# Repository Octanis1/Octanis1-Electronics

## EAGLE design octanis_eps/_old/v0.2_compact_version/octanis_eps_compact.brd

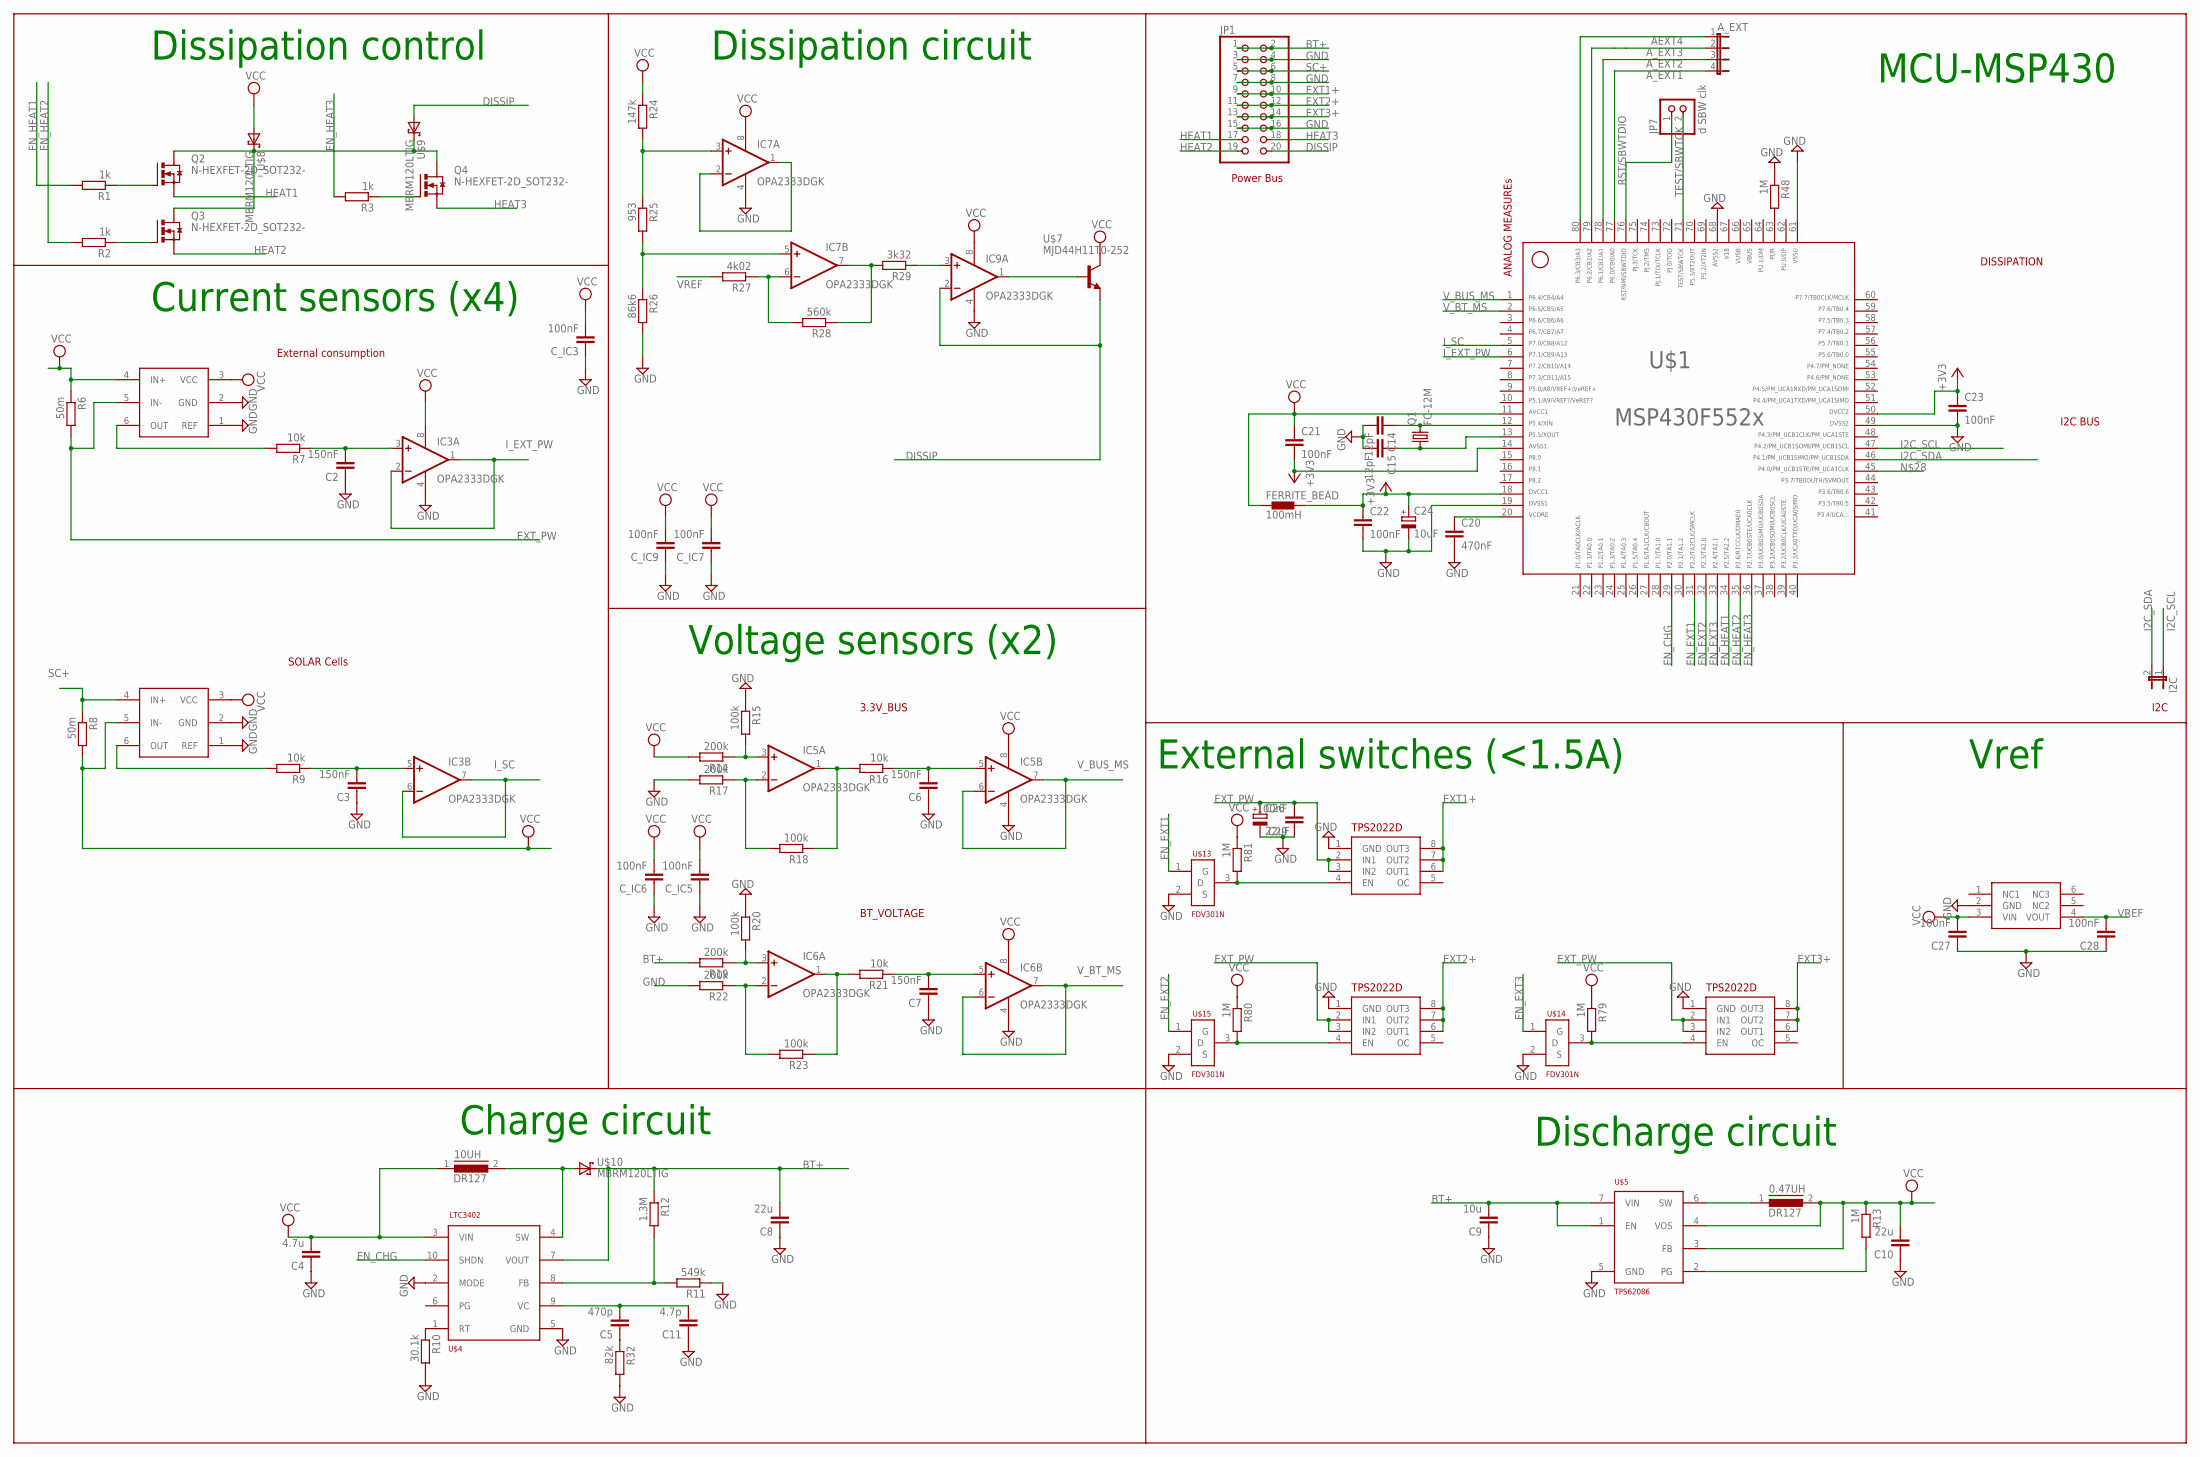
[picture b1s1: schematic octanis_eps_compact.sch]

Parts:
0.47UH, 10UH: DR127
A_EXT: JP4E; JP4
C2, C3, C6, C7: 150nF; C0603
C4: 4.7u; C1206
C5: 470p; C0603
C8: 22u; C0603
C9: 10u; C1206
C10: 22u; C1206
C11: 4.7p; C0603
C14, C15: 12pF; C0603
C20: 470nF; C0603
C21, C22, C23, C27, C28, C29: 100nF; C0603
C24: 10uF; A/3216-18R
C26: 22uF; A/3216-18R
C_IC3, C_IC5, C_IC6, C_IC7, C_IC9: 100nF; C0603
FERRITE_BEAD: 100mH; 0402
I2C: JP1E; JP1
IC3, IC5, IC6, IC7, IC9: OPA2333DGK; MSOP08
JP1: PINHD-2X10; 2X10
JP7: d SBW clk; 1X02
Q1: FC-12M
Q2, Q3, Q4: N-HEXFET-2D_SOT232-; SOT223
R1, R2, R3: 1k; R0603
R6, R8: 50m; R1206
R7, R9, R16, R21: 10k; R0603
R10: 30.1k; R0603
R11: 549k; R0603
R12: 1.3M; R0603
R13, R48, R79, R80, R81: 1M; R0603
R14, R17, R19, R22: 200k; R0603
R15, R18, R20, R23: 100k; R0603
R24: 147k; R0603
R25: 953; R0603
R26: 86k6; R0603
R27: 4k02; R0603
R28: 560k; R0603
R29: 3k32; R0603
R32: 82k; R0603
U$1: F552X---PN80; PN80
U$2, U$3: INA213; SC70-6
U$4: LTC3402; MSOP10
U$5: TPS62086; QFN-7
U$7: MJD44H11T0-252; TO252
U$8, U$9, U$10: MBRM120LTIG; DO216AA
U$13, U$14, U$15: FDV301N; SOT23
U$16, U$17, U$18: TPS2022D; SO8
U$19: ADR127B; TSOT23-6

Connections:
65: U$1.65
66: U$1.66
67: U$1.67
+3V3: C21.2, C22.1, C23.1, C24.+, FERRITE_BEAD.2, U$1.14, U$1.18, U$1.50
AEXT4: A_EXT.1, U$1.80
A_EXT1: A_EXT.4, U$1.77
A_EXT2: A_EXT.3, U$1.78
A_EXT3: A_EXT.2, U$1.79
BT+: C8.2, C9.2, JP1.1, JP1.2, R12.1, R19.2, U$4.7 (VOUT), U$5.1 (EN), U$5.7 (VIN), U$10.C (K)
DISSIP: IC9.2 (-IN), JP1.20, U$7.3 (E), U$9.A
EN_CHG: U$1.29, U$4.10 (SHDN)
EN_EXT1: U$1.31, U$13.1 (G)
EN_EXT2: U$1.32, U$15.1 (G)
EN_EXT3: U$1.33, U$14.1 (G)
EN_HEAT1: R1.2, U$1.34
EN_HEAT2: R2.2, U$1.35
EN_HEAT3: R3.2, U$1.36
EXT1+: JP1.9, JP1.10, U$16.6 (OUT1), U$16.7 (OUT2), U$16.8 (OUT3)
EXT2+: JP1.11, JP1.12, U$17.6 (OUT1), U$17.7 (OUT2), U$17.8 (OUT3)
EXT3+: JP1.13, JP1.14, U$18.6 (OUT1), U$18.7 (OUT2), U$18.8 (OUT3)
EXT_PW: C26.+, C29.2, R6.2, U$2.5 (IN-), U$16.2 (IN1), U$16.3 (IN2), U$17.2 (IN1), U$17.3 (IN2), U$18.2 (IN1), U$18.3 (IN2)
GND: C2.1, C3.1, C4.1, C6.1, C7.1, C8.1, C9.1, C10.1, C11.1, C14.2, C15.2, C20.2, C22.2, C23.2, C24.-, C26.-, C27.1, C28.1, C29.1, C_IC3.1, C_IC5.1, C_IC6.1, C_IC7.1, C_IC9.1, IC3.4 (V-), IC5.4 (V-), IC6.4 (V-), IC7.4 (V-), IC9.4 (V-), JP1.3, JP1.4, JP1.7, JP1.8, JP1.15, JP1.16, R10.2, R11.1, R15.1, R17.2, R20.1, R22.2, R26.2, R32.2, R48.1, U$1.19, U$1.49, U$1.61, U$1.68, U$2.1 (REF), U$2.2 (GND), U$3.1 (REF), U$3.2 (GND), U$4.2 (MODE), U$4.5 (GND), U$5.5 (GND), U$13.2 (S), U$14.2 (S), U$15.2 (S), U$16.1 (GND), U$17.1 (GND), U$18.1 (GND), U$19.2 (GND)
HEAT1: JP1.17, Q2.3 (S)
HEAT2: JP1.19, Q3.3 (S)
HEAT3: JP1.18, Q4.3 (S)
I2C_SCL: I2C.1, U$1.47
I2C_SDA: I2C.2, U$1.46
I_EXT_PW: IC3.1 (OUT), IC3.2 (-IN), U$1.6
I_SC: IC3.6 (-IN), IC3.7 (OUT), U$1.5
unnamed: R7.2, U$2.6 (OUT)
unnamed: R9.2, U$3.6 (OUT)
unnamed: R10.1, U$4.1 (RT)
unnamed: C5.1, R32.1
unnamed: Q2.2 (D), Q2.4 (D), Q3.2 (D), Q3.4 (D), Q4.2 (D), Q4.4 (D), U$8.C (K), U$9.C (K)
unnamed: C2.2, IC3.3 (+IN), R7.1
unnamed: C3.2, IC3.5 (+IN), R9.1
unnamed: C5.2, C11.2, U$4.9 (VC)
unnamed: C7.2, IC6.5 (+IN), R21.1
unnamed: IC6.1 (OUT), R21.2, R23.1
unnamed: C6.2, IC5.5 (+IN), R16.1
unnamed: IC5.1 (OUT), R16.2, R18.1
unnamed: IC5.2 (-IN), R17.1, R18.2
unnamed: IC5.3 (+IN), R14.1, R15.2
unnamed: IC6.2 (-IN), R22.1, R23.2
unnamed: IC6.3 (+IN), R19.1, R20.2
unnamed: IC7.1 (OUT), IC7.2 (-IN)
unnamed: IC7.3 (+IN), R24.2, R25.1
unnamed: IC7.5 (+IN), R25.2, R26.1
unnamed: IC7.6 (-IN), R27.1, R28.2
unnamed: IC7.7 (OUT), R28.1, R29.2
unnamed: IC9.3 (+IN), R29.1
unnamed: R11.2, R12.2, U$4.8 (FB)
unnamed: 10UH.2, U$4.4 (SW), U$10.A
unnamed: R13.2, U$5.2 (PG)
unnamed: 0.47UH.1, U$5.6 (SW)
unnamed: R48.2, U$1.63
unnamed: Q2.1 (G), R1.1
unnamed: Q3.1 (G), R2.1
unnamed: R80.2, U$15.3 (D), U$17.4 (EN)
unnamed: Q4.1 (G), R3.1
unnamed: IC9.1 (OUT), U$7.1 (B)
unnamed: C14.1, Q1.2, U$1.12
unnamed: C20.1, U$1.20
unnamed: C15.1, Q1.1, U$1.13
unnamed: R81.2, U$13.3 (D), U$16.4 (EN)
unnamed: R79.2, U$14.3 (D), U$18.4 (EN)
RST/SBWTDIO: JP7.1, U$1.76
SC+: JP1.5, JP1.6, R8.1, U$3.4 (IN+)
TEST/SBWTCK: JP7.2, U$1.71
VCC: 0.47UH.2, 10UH.1, C4.2, C10.2, C21.1, C27.2, C_IC3.2, C_IC5.2, C_IC6.2, C_IC7.2, C_IC9.2, FERRITE_BEAD.1, IC3.8 (V+), IC5.8 (V+), IC6.8 (V+), IC7.8 (V+), IC9.8 (V+), R6.1, R8.2, R13.1, R14.2, R24.1, R79.1, R80.1, R81.1, U$1.11, U$2.3 (VCC), U$2.4 (IN+), U$3.3 (VCC), U$3.5 (IN-), U$4.3 (VIN), U$5.3 (FB), U$5.4 (VOS), U$7.2 (C), U$8.A, U$19.3 (VIN)
VREF: C28.2, R27.2, U$19.4 (VOUT)
V_BT_MS: IC6.6 (-IN), IC6.7 (OUT), U$1.2
V_BUS_MS: IC5.6 (-IN), IC5.7 (OUT), U$1.1

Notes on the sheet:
Vref
Current sensors (x4)
SOLAR Cells
3.3V_BUS
Charge circuit
Discharge circuit
External switches (<1.5A)
MCU-MSP430
Voltage sensors (x2)
BT_VOLTAGE
Dissipation circuit
I2C BUS
ANALOG MEASUREs
I2C
External consumption
Dissipation control
DISSIPATION
Power Bus

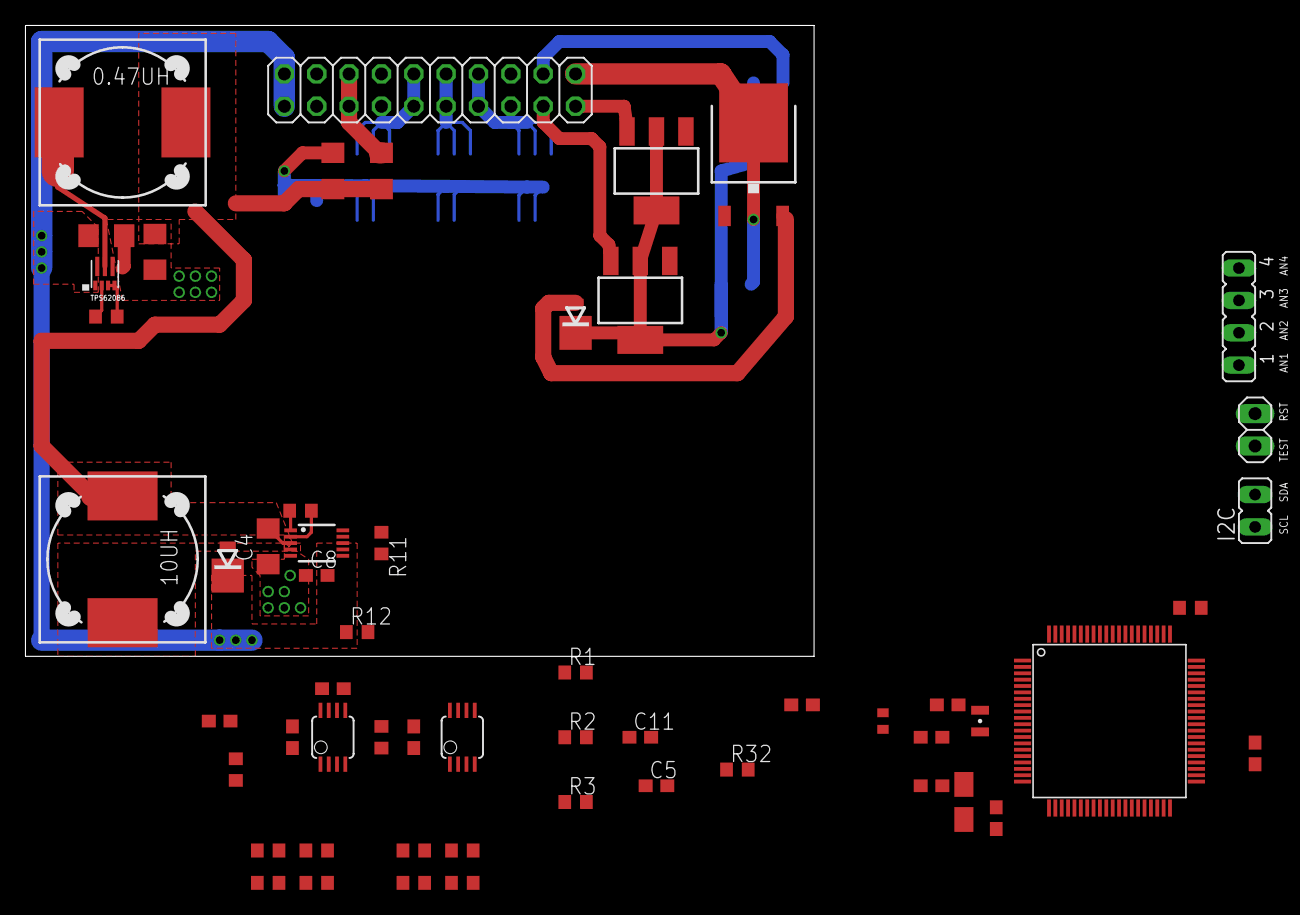
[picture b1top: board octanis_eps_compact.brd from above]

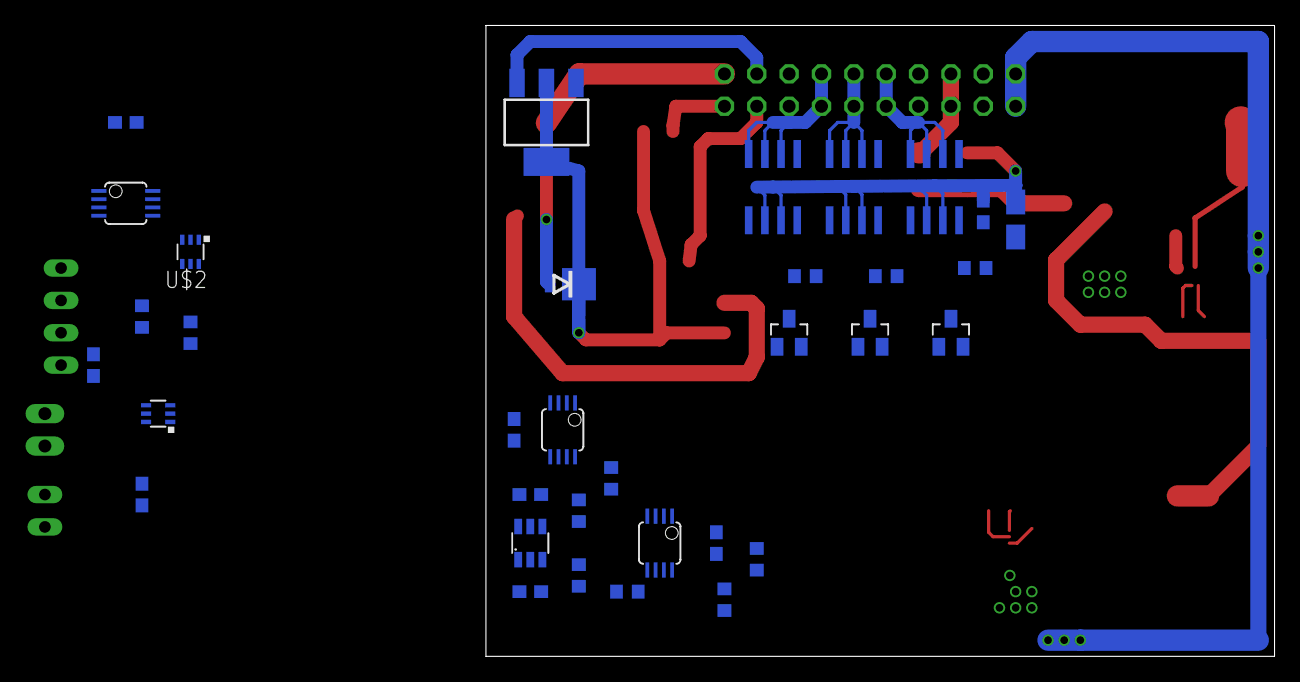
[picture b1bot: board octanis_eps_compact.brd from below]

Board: 4 copper layers, 61.9 x 49.5 mm, 90 parts (34 on the bottom side), 70 nets.

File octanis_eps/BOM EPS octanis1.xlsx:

BOM EPS Octanis1
Active components
Reference | Unit Price (CHF) | Qty | Total price | Manufacturer | Package | Provider | Description
TPS62086RLTT | 6.35 | 1.0 | 6.35 | TI | VQFN-7 | Farnell | 3.3V 3A buck converter (discharge)
LTC3402EMS#PBF | 11.1 | 1.0 | 11.1 | Linear Devices | MSOP10 | Farnell | Adjustable boost converter 2A (charge
MSP430G2744IDA38R | 2.85 | 1.0 | 2.85 | TI | TSSOP38 | TI | MCU
INA213AIDCKT | 1.7 | 2.0 | 3.4 | TI | SC70-6 | Farnell | Gain 50 current sensor 35µA polarization
TPS2022D | 3.5 | 3.0 | 10.5 | TI | SOIC8 | Farnell | 1.5A distribution switch
ADR127BUJZ-REEL7 | 10.15 | 1.0 | 10.15 | Analog Devices | TSOT23-6 | Farnell | Precision 1.25V voltage reference
OPA2333AIDGKT | 3.6 | 3.0 | 10.8 | TI | MSOP8 | Farnell | Low power OPA 2 channels
FDV301N | 0.038 | 3.0 | 0.114 | Farichild | SOT-23 | Farnell | N canal MOSFET
IRLL024NPBF | 1.25 | 3.0 | 3.75 | IR | SOT-223 | Farnell | N hexfet 2V threshold
MJD44H11T4 | 0.713 | 1.0 | 0.713 | ST micro | TO-252 | Farnell | BJT
Reference | Unit Price (CHF) | Qty | Total price | Manufacturer | Package | Provider | Description
1kOhm | 0.015 | 3.0 | 0.045 | - | 603.0 | Farnell
50mOhm 0.1% | 0.1 | 2.0 | 0.2 | - | 1206.0 | Farnell | current shunts precision resistor
10kOhm 0.1% | 0.03 | 4.0 | 0.12 | - | 603.0 | Farnell
100kOhm | 0.015 | 4.0 | 0.06 | - | 603.0 | Farnell
200kOhm | 0.015 | 4.0 | 0.06 | - | 603.0 | Farnell
147kOhm 0.1% | 0.03 | 1.0 | 0.03 | - | 603.0 | Farnell
953Ohm 0.1% | 0.03 | 1.0 | 0.03 | - | 603.0 | Farnell
86k6Ohm 0.1% | 0.5 | 1.0 | 0.5 | - | 603.0 | Farnell
4k02Ohm 0.1% | 0.5 | 1.0 | 0.5 | - | 603.0 | Farnell
560kOhm 0.1% | 0.1 | 1.0 | 0.1 | - | 603.0 | Farnell
3k32Ohm 0.1% | 0.5 | 1.0 | 0.5 | - | 603.0 | Farnell
30k1Ohm 0.1% | 0.5 | 1.0 | 0.5 | - | 603.0 | Farnell
1.3MOhm 0.1% | 0.5 | 1.0 | 0.5 | - | 603.0 | Farnell
549kOhm 0.1% | 0.5 | 1.0 | 0.5 | - | 603.0 | Farnell
82kOhm 0.1% | 0.5 | 1.0 | 0.5 | - | 603.0 | Farnell
1MOhm | 0.015 | 1.0 | 0.015 | - | 603.0 | Farnell
MBRM120LT1G | 0.9 | 3.0 | 2.7 | - | D0216AA | Farnell | shottky
150nF | 0.03 | 4.0 | 0.12 | - | 603.0 | Farnell
100nF | 0.03 | 8.0 | 0.24 | - | 603.0 | Farnell
12pF 1% | 0.5 | 2.0 | 1 | - | 603.0 | Farnell
10uF | 0.5 | 1.0 | 0.5 | - | A/3216-18R | Farnell | polarized capacitor
22uF | 0.5 | 1.0 | 0.5 | - | A/3216-18R | Farnell | polarized capacitor
470pF | 0.003 | 1.0 | 0.003 | - | 603.0 | Farnell
4.7pF | 0.003 | 1.0 | 0.003 | - | 603.0 | Farnell
4.7uF | 0.5 | 1.0 | 0.5 | - | 1206.0 | Farnell | X5R or X7R family recommended
22uF | 0.5 | 2.0 | 1 | - | 603.0 | Farnell | X5R or X7R family recommended
10uF | 0.5 | 2.0 | 1 | - | 1206.0 | Farnell | X5R or X7R family recommended
10uH | 1.25 | 1.0 | 1.25 | Coiltronics | DR127 | Farnell | Power inductor 10uH
DR127-R47-R. | 1.2 | 1.0 | 1.2 | Coiltronics | DR128 | Farnell | Power inductor 0.47uH
32Mhz crystal | 0.5 | 1.0 | 0.5 | - | FC-12M | Farnell | Crystal
 |  | Total | 74.403

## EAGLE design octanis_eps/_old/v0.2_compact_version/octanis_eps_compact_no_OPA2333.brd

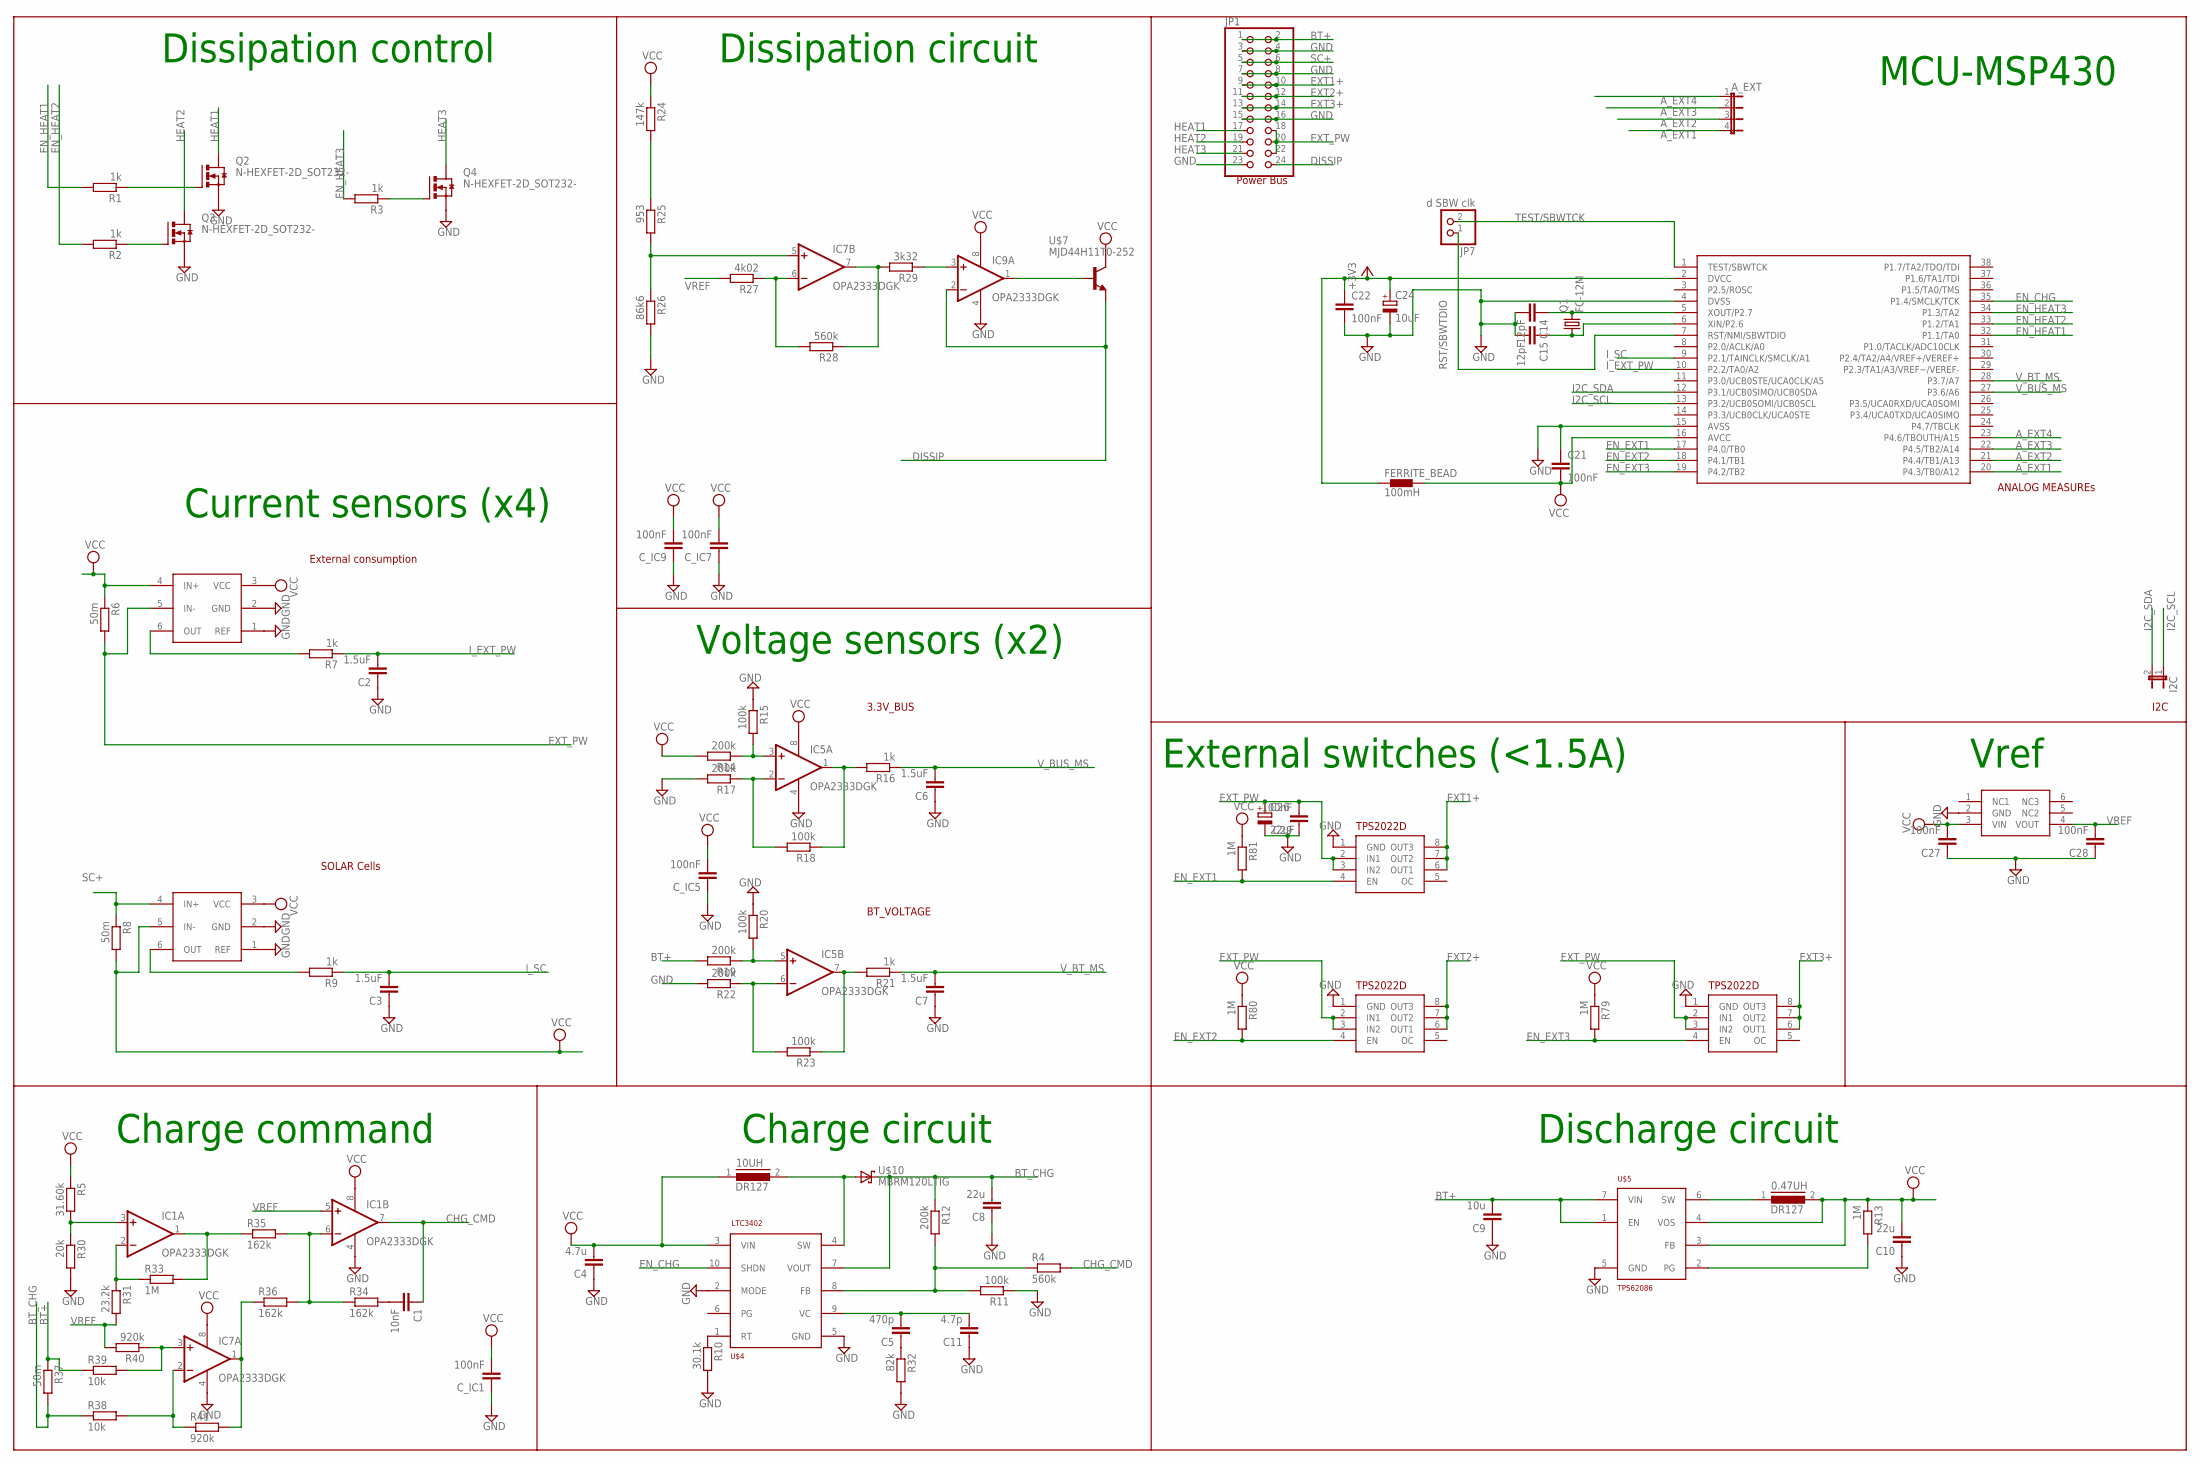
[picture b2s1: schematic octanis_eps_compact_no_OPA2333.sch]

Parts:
0.47UH, 10UH: DR127
A_EXT: JP4E; JP4
C1: 10nF; C0603
C2, C3, C6, C7: 1.5uF; C0603
C4: 4.7u; C1206
C5: 470p; C0603
C8: 22u; C0603
C9: 10u; C1206
C10: 22u; C1206
C11: 4.7p; C0603
C14, C15: 12pF; C0603
C21, C22, C27, C28, C29: 100nF; C0603
C24: 10uF; A/3216-18R
C26: 22uF; A/3216-18R
C_IC1, C_IC5, C_IC7, C_IC9: 100nF; C0603
FERRITE_BEAD: 100mH; 0402
I2C: JP1E; JP1
IC1, IC5, IC7, IC9: OPA2333DGK; MSOP08
JP1: PINHD-2X12; 2X12
JP7: d SBW clk; 1X02
Q1: FC-12M
Q2, Q3, Q4: N-HEXFET-2D_SOT232-; SOT223
R1, R2, R3, R7, R9, R16, R21: 1k; R0603
R4, R28: 560k; R0603
R5: 31.60k; R0603
R6, R8, R37: 50m; R1206
R10: 30.1k; R0603
R11, R15, R18, R20, R23: 100k; R0603
R12, R14, R17, R19, R22: 200k; R0603
R13, R33, R79, R80, R81: 1M; R0603
R24: 147k; R0603
R25: 953; R0603
R26: 86k6; R0603
R27: 4k02; R0603
R29: 3k32; R0603
R30: 20k; R0603
R31: 23.2k; R0603
R32: 82k; R0603
R34, R35, R36: 162k; R0603
R38, R39: 10k; R0603
R40, R41: 920k; R0603
U$2, U$3: INA213; SC70-6
U$4: LTC3402; MSOP10
U$5: TPS62086; QFN-7
U$6: MSP430G2544; TSSOP38
U$7: MJD44H11T0-252; TO252
U$10: MBRM120LTIG; DO216AA
U$16, U$17, U$18: TPS2022D; SO8
U$19: ADR127B; TSOT23-6

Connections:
+3V3: C22.1, C24.+, FERRITE_BEAD.1, U$6.2 (DVCC)
A_EXT1: A_EXT.4, U$6.20 (P4.3/TB0/A12)
A_EXT2: A_EXT.3, U$6.21 (P4.4/TB1/A13)
A_EXT3: A_EXT.2, U$6.22 (P4.5/TB2/A14)
A_EXT4: A_EXT.1, U$6.23 (P4.6/TBOUTH/A15)
BT+: C9.2, JP1.1, JP1.2, R19.2, R37.1, R39.1, U$5.1 (EN), U$5.7 (VIN)
BT_CHG: C8.2, R12.1, R37.2, R38.1, U$4.7 (VOUT), U$10.C (K)
CHG_CMD: C1.1, IC1.7 (OUT), R4.2
DISSIP: IC9.2 (-IN), JP1.24, U$7.3 (E)
EN_CHG: U$4.10 (SHDN), U$6.35 (P1.4/SMCLK/TCK)
EN_EXT1: R81.2, U$6.17 (P4.0/TB0), U$16.4 (EN)
EN_EXT2: R80.2, U$6.18 (P4.1/TB1), U$17.4 (EN)
EN_EXT3: R79.2, U$6.19 (P4.2/TB2), U$18.4 (EN)
EN_HEAT1: R1.2, U$6.32 (P1.1/TA0)
EN_HEAT2: R2.2, U$6.33 (P1.2/TA1)
EN_HEAT3: R3.2, U$6.34 (P1.3/TA2)
EXT1+: JP1.9, JP1.10, U$16.6 (OUT1), U$16.7 (OUT2), U$16.8 (OUT3)
EXT2+: JP1.11, JP1.12, U$17.6 (OUT1), U$17.7 (OUT2), U$17.8 (OUT3)
EXT3+: JP1.13, JP1.14, U$18.6 (OUT1), U$18.7 (OUT2), U$18.8 (OUT3)
EXT_PW: C26.+, C29.2, JP1.18, JP1.20, JP1.22, R6.2, U$2.5 (IN-), U$16.2 (IN1), U$16.3 (IN2), U$17.2 (IN1), U$17.3 (IN2), U$18.2 (IN1), U$18.3 (IN2)
GND: C2.1, C3.1, C4.1, C6.1, C7.1, C8.1, C9.1, C10.1, C11.1, C14.2, C15.2, C21.1, C22.2, C24.-, C26.-, C27.1, C28.1, C29.1, C_IC1.1, C_IC5.1, C_IC7.1, C_IC9.1, IC1.4 (V-), IC5.4 (V-), IC7.4 (V-), IC9.4 (V-), JP1.3, JP1.4, JP1.7, JP1.8, JP1.15, JP1.16, JP1.23, Q2.3 (S), Q3.3 (S), Q4.3 (S), R10.2, R11.1, R15.1, R17.2, R20.1, R22.2, R26.2, R30.2, R32.2, U$2.1 (REF), U$2.2 (GND), U$3.1 (REF), U$3.2 (GND), U$4.2 (MODE), U$4.5 (GND), U$5.5 (GND), U$6.4 (DVSS), U$6.15 (AVSS), U$16.1 (GND), U$17.1 (GND), U$18.1 (GND), U$19.2 (GND)
HEAT1: JP1.17, Q2.2 (D), Q2.4 (D)
HEAT2: JP1.19, Q3.2 (D), Q3.4 (D)
HEAT3: JP1.21, Q4.2 (D), Q4.4 (D)
I2C_SCL: I2C.1, U$6.13 (P3.2/UCB0SOMI/UCB0SCL)
I2C_SDA: I2C.2, U$6.12 (P3.1/UCB0SIMO/UCB0SDA)
I_EXT_PW: C2.2, R7.1, U$6.10 (P2.2/TA0/A2)
I_SC: C3.2, R9.1, U$6.9 (P2.1/TAINCLK/SMCLK/A1)
unnamed: R7.2, U$2.6 (OUT)
unnamed: R9.2, U$3.6 (OUT)
unnamed: R10.1, U$4.1 (RT)
unnamed: C5.1, R32.1
unnamed: IC7.1 (OUT), R36.1, R41.2
unnamed: IC1.3 (+IN), R5.2, R30.1
unnamed: IC1.2 (-IN), R31.1, R33.1
unnamed: C5.2, C11.2, U$4.9 (VC)
unnamed: IC1.1 (OUT), R33.2, R35.1
unnamed: IC5.7 (OUT), R21.2, R23.1
unnamed: IC1.6 (-IN), R34.1, R35.2, R36.2
unnamed: IC5.1 (OUT), R16.2, R18.1
unnamed: IC5.2 (-IN), R17.1, R18.2
unnamed: IC5.3 (+IN), R14.1, R15.2
unnamed: IC5.6 (-IN), R22.1, R23.2
unnamed: IC5.5 (+IN), R19.1, R20.2
unnamed: IC7.2 (-IN), R38.2, R41.1
unnamed: R24.2, R25.1
unnamed: IC7.5 (+IN), R25.2, R26.1
unnamed: IC7.6 (-IN), R27.1, R28.2
unnamed: IC7.7 (OUT), R28.1, R29.2
unnamed: IC9.3 (+IN), R29.1
unnamed: R4.1, R11.2, R12.2, U$4.8 (FB)
unnamed: 10UH.2, U$4.4 (SW), U$10.A
unnamed: R13.2, U$5.2 (PG)
unnamed: 0.47UH.1, U$5.6 (SW)
unnamed: C1.2, R34.2
unnamed: IC7.3 (+IN), R39.2, R40.1
unnamed: Q2.1 (G), R1.1
unnamed: Q3.1 (G), R2.1
unnamed: Q4.1 (G), R3.1
unnamed: IC9.1 (OUT), U$7.1 (B)
unnamed: C14.1, Q1.2, U$6.5 (XOUT/P2.7)
unnamed: C15.1, Q1.1, U$6.6 (XIN/P2.6)
RST/SBWTDIO: JP7.1, U$6.7 (RST/NMI/SBWTDIO)
SC+: JP1.5, JP1.6, R8.1, U$3.4 (IN+)
TEST/SBWTCK: JP7.2, U$6.1 (TEST/SBWTCK)
VCC: 0.47UH.2, 10UH.1, C4.2, C10.2, C21.2, C27.2, C_IC1.2, C_IC5.2, C_IC7.2, C_IC9.2, FERRITE_BEAD.2, IC1.8 (V+), IC5.8 (V+), IC7.8 (V+), IC9.8 (V+), R5.1, R6.1, R8.2, R13.1, R14.2, R24.1, R79.1, R80.1, R81.1, U$2.3 (VCC), U$2.4 (IN+), U$3.3 (VCC), U$3.5 (IN-), U$4.3 (VIN), U$5.3 (FB), U$5.4 (VOS), U$6.16 (AVCC), U$7.2 (C), U$19.3 (VIN)
VREF: C28.2, IC1.5 (+IN), R27.2, R31.2, R40.2, U$19.4 (VOUT)
V_BT_MS: C7.2, R21.1, U$6.28 (P3.7/A7)
V_BUS_MS: C6.2, R16.1, U$6.27 (P3.6/A6)

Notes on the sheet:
Vref
Current sensors (x4)
SOLAR Cells
3.3V_BUS
Charge circuit
Discharge circuit
External switches (<1.5A)
MCU-MSP430
Voltage sensors (x2)
BT_VOLTAGE
Dissipation circuit
ANALOG MEASUREs
I2C
External consumption
Dissipation control
Power Bus
Charge command

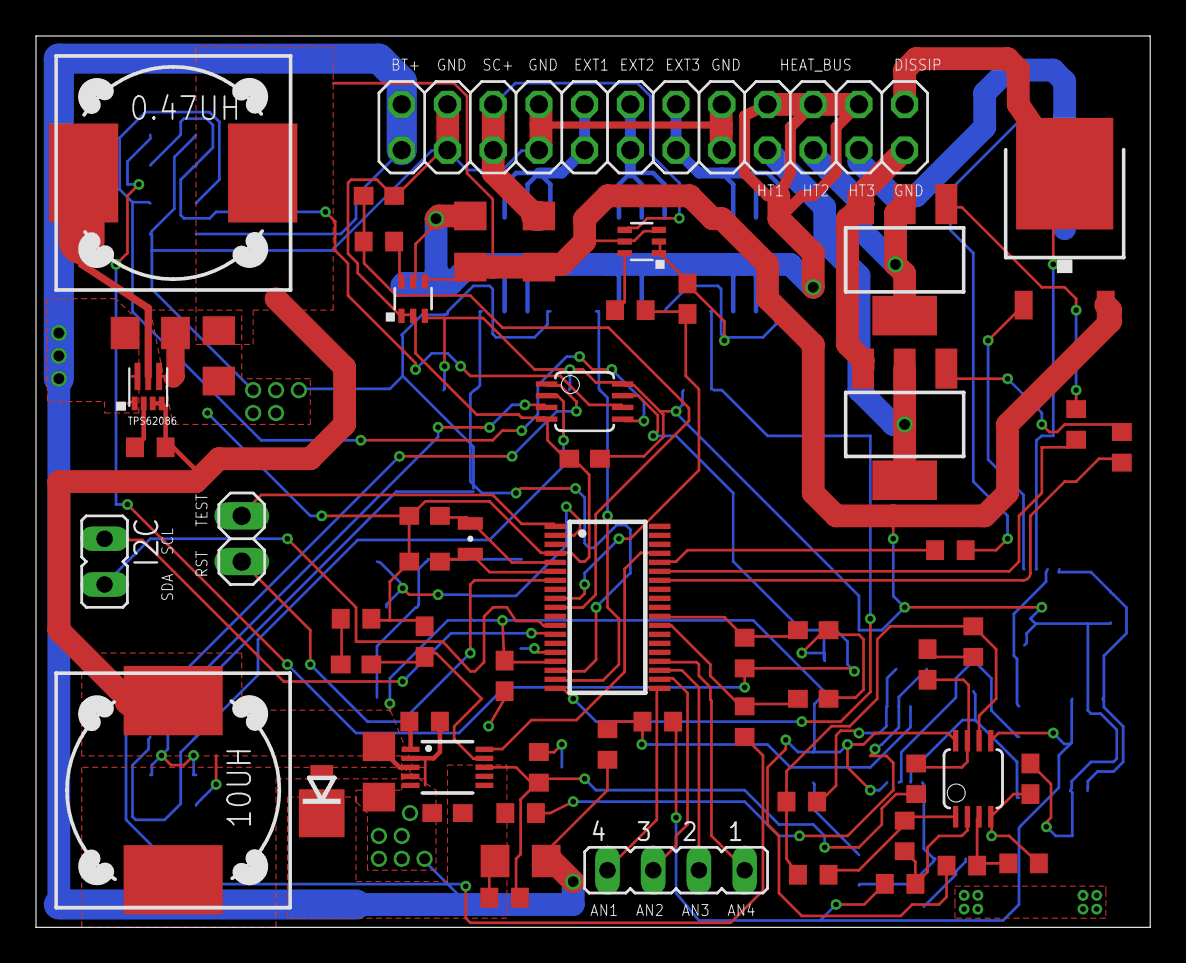
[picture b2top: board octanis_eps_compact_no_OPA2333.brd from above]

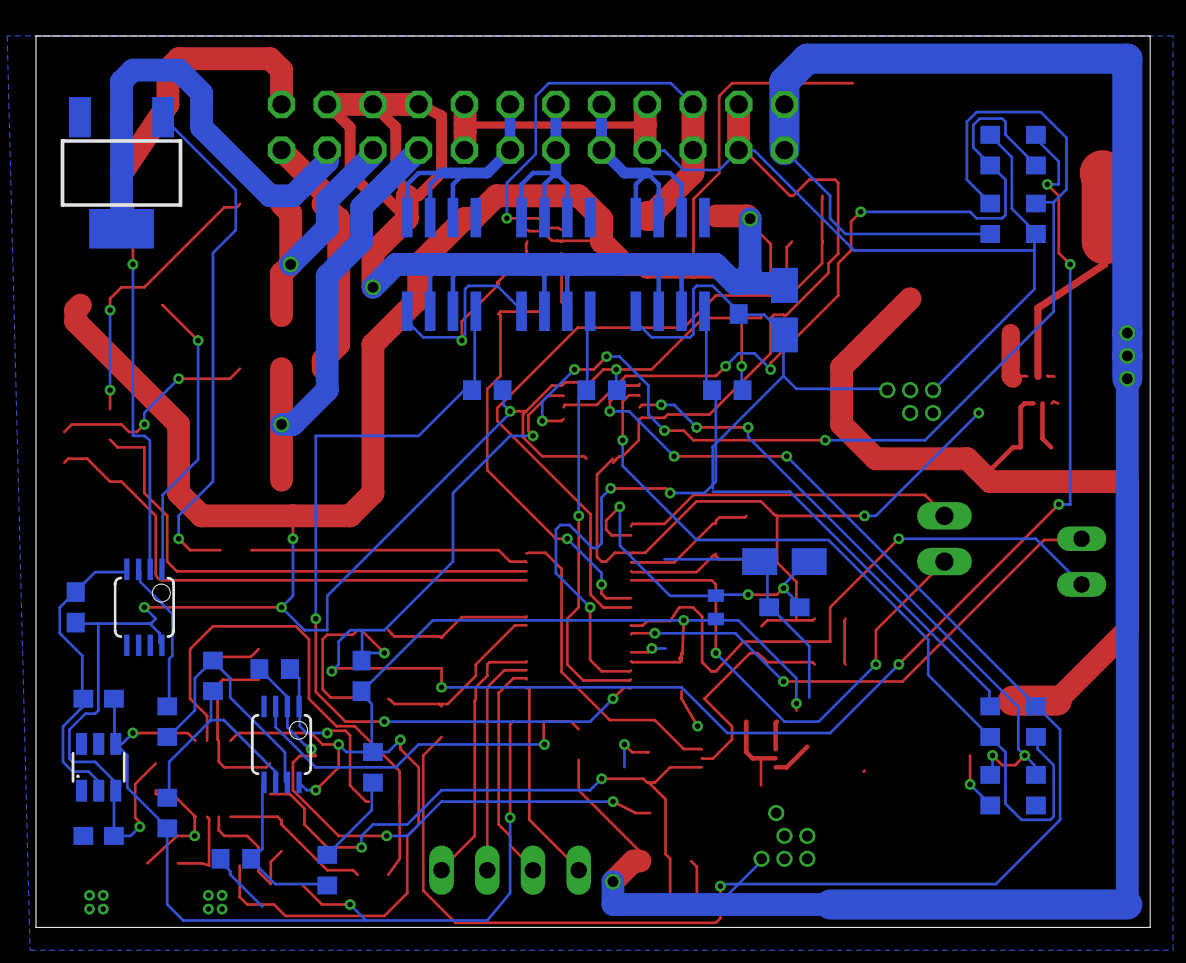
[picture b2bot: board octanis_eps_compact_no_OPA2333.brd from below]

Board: 4 copper layers, 61.9 x 49.5 mm, 94 parts (34 on the bottom side), 69 nets.

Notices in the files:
parts and their libraries:
SparkFun-Sensors: Licensing: CC v3.0 Share-Alike You are welcome to use this library for commercial purposes.
